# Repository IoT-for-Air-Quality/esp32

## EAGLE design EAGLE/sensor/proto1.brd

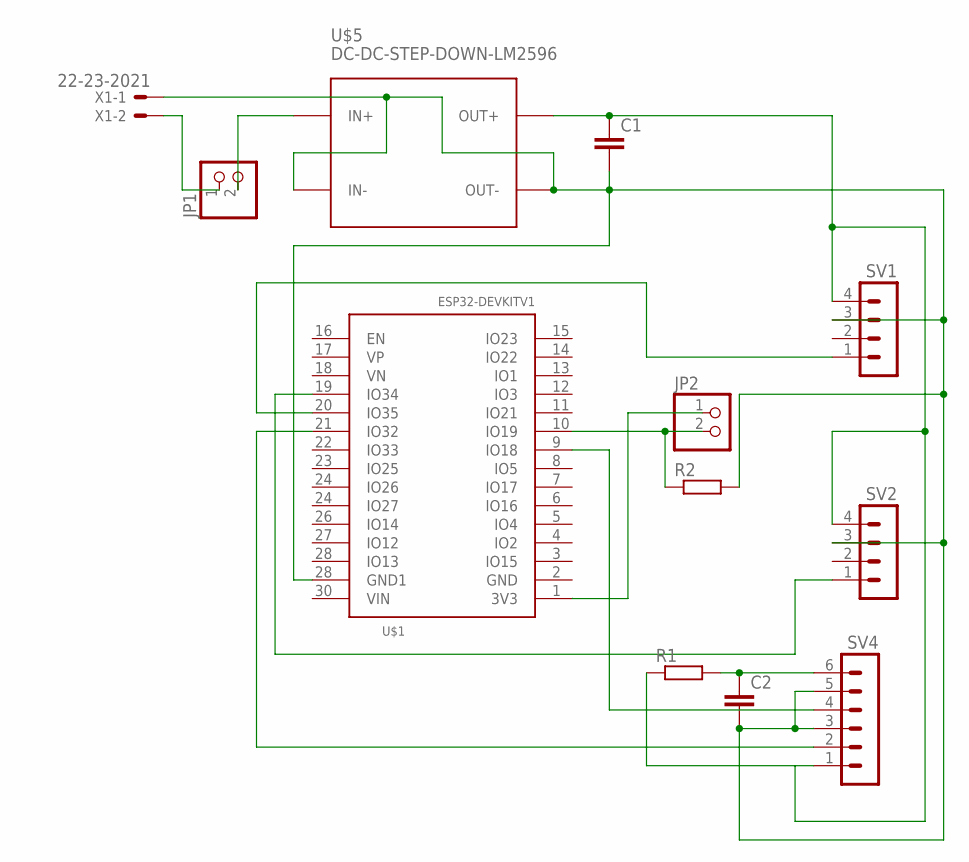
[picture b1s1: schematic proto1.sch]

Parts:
C1, C2: C2,5-3; C2.5-3
JP1, JP2: PINHD-1X2/90; 1X02/90
R1, R2: R-EU_0207/10; 0207/10
SV1, SV2: MA04-1
SV4: MA06-1
U$1: ESP32DEVKITV1; ESP32-DEVKITV1
U$5: DC-DC-STEP-DOWN-LM2596
X1: 22-23-2021

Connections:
unnamed: C1.1, R1.1, SV1.4, SV2.4, SV4.1, U$5.OUT+
unnamed: C1.2, C2.2, R2.2, SV1.3, SV2.3, SV4.3, SV4.5, U$1.28 (IO13), U$5.IN-, U$5.OUT-, X1.1
unnamed: JP2.2, R2.1, U$1.10 (IO19)
unnamed: JP2.1, U$1.1 (3V3)
unnamed: SV4.4, U$1.9 (IO18)
unnamed: C2.1, R1.2, SV4.6
unnamed: SV4.2, U$1.21 (IO32)
unnamed: JP1.1, X1.2
unnamed: SV1.1, U$1.20 (IO35)
unnamed: JP1.2, U$5.IN+
unnamed: SV2.1, U$1.19 (IO34)

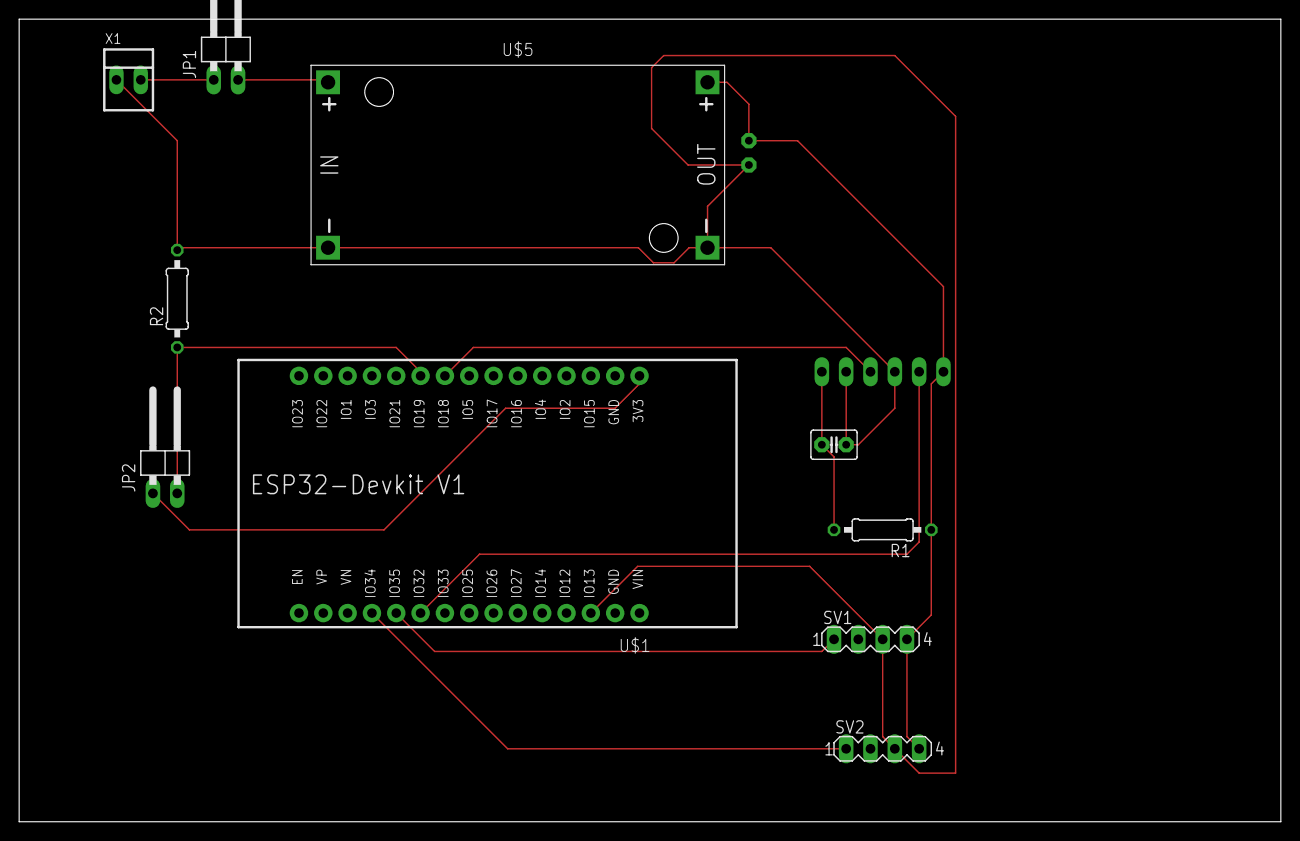
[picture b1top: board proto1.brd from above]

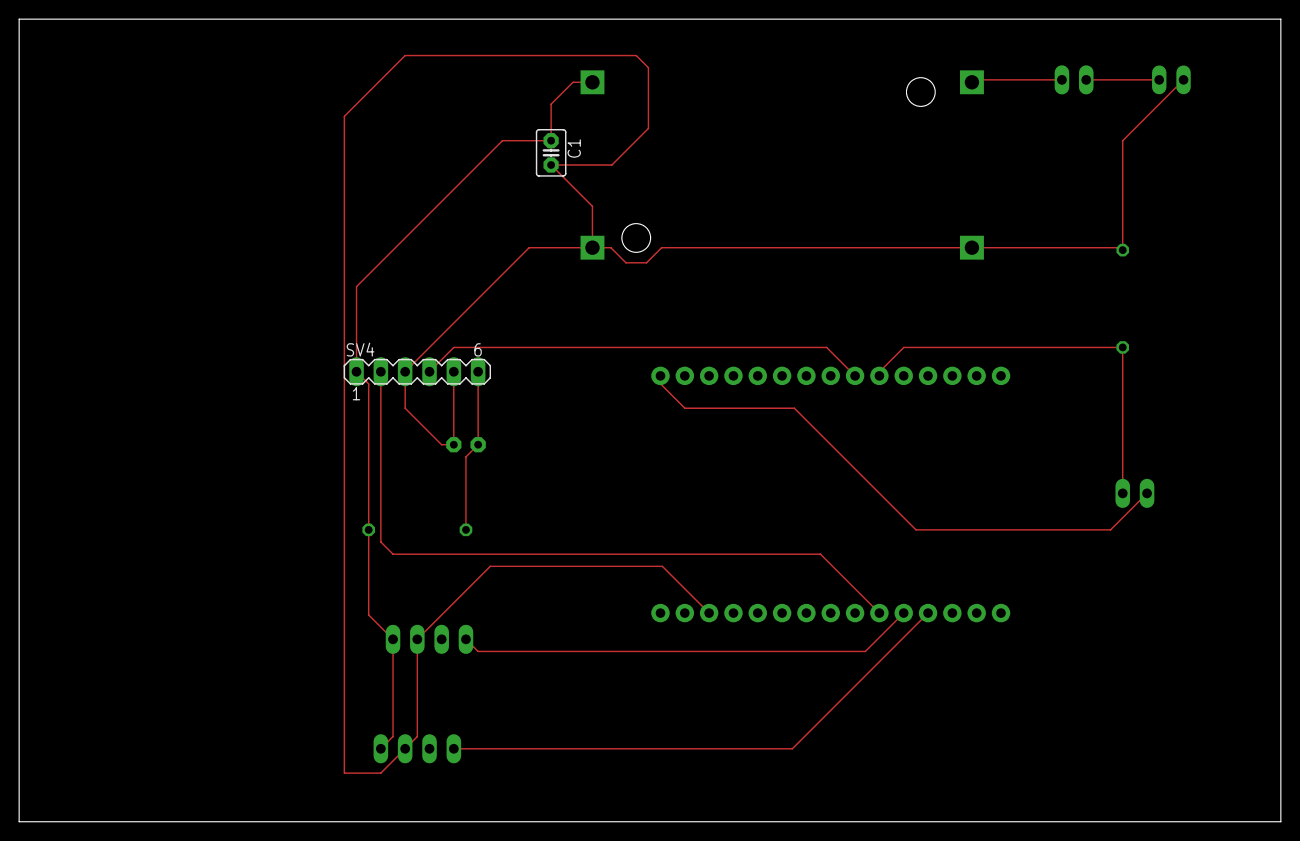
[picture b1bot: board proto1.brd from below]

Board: 2 copper layers, 131.8 x 83.8 mm, 12 parts (2 on the bottom side), 11 nets.

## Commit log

2021-09-28 Fixed code
2021-09-28 Eagle files added
2021-10-26 BT to BTLE
2021-11-02 MQ7 calibrated. MQ135 fail
2021-11-08 Values updated
2021-11-14 Files system and OS
2021-11-15 Wifi allways enabled
2021-11-15 before sending data to server offline
2021-11-15 Working lose connection device
2021-11-16 Suppourt for alerts to smartphone

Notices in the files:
parts and their libraries:
diy-modules: Released under the Creative Commons Attribution 4.0 International License: http://creativecommons.org/licenses/by/4.0
